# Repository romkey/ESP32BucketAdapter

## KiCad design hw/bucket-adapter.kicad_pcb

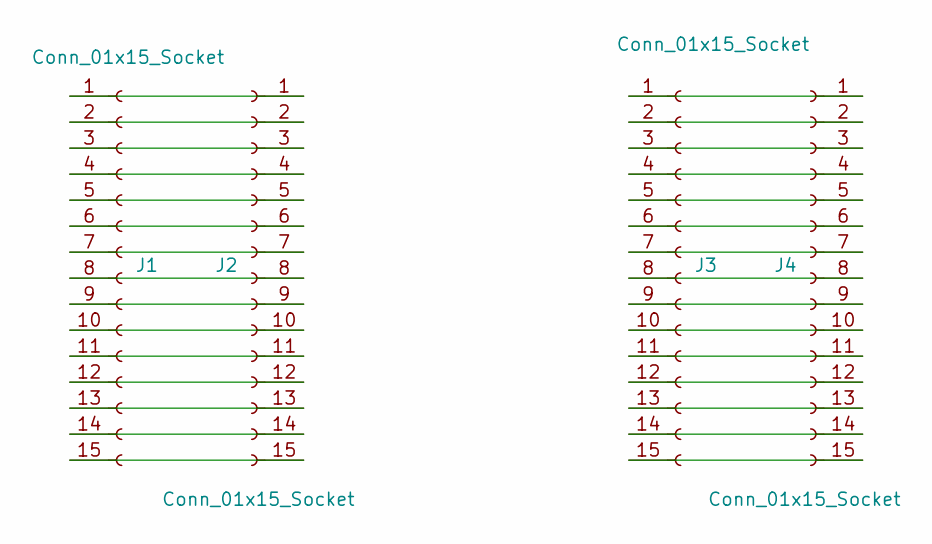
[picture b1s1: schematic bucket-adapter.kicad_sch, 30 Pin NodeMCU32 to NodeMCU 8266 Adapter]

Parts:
J1, J2, J3, J4: Conn_01x15_Socket; PinSocket_1x15_P2.54mm_Vertical

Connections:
unnamed: J1.1, J2.1
unnamed: J1.2, J2.2
unnamed: J1.3, J2.3
unnamed: J1.4, J2.4
unnamed: J1.5, J2.5
unnamed: J1.6, J2.6
unnamed: J1.7, J2.7
unnamed: J1.8, J2.8
unnamed: J1.9, J2.9
unnamed: J1.10, J2.10
unnamed: J1.11, J2.11
unnamed: J1.12, J2.12
unnamed: J1.13, J2.13
unnamed: J1.14, J2.14
unnamed: J1.15, J2.15
unnamed: J3.1, J4.1
unnamed: J3.2, J4.2
unnamed: J3.3, J4.3
unnamed: J3.4, J4.4
unnamed: J3.5, J4.5
unnamed: J3.6, J4.6
unnamed: J3.7, J4.7
unnamed: J3.8, J4.8
unnamed: J3.9, J4.9
unnamed: J3.10, J4.10
unnamed: J3.11, J4.11
unnamed: J3.12, J4.12
unnamed: J3.13, J4.13
unnamed: J3.14, J4.14
unnamed: J3.15, J4.15

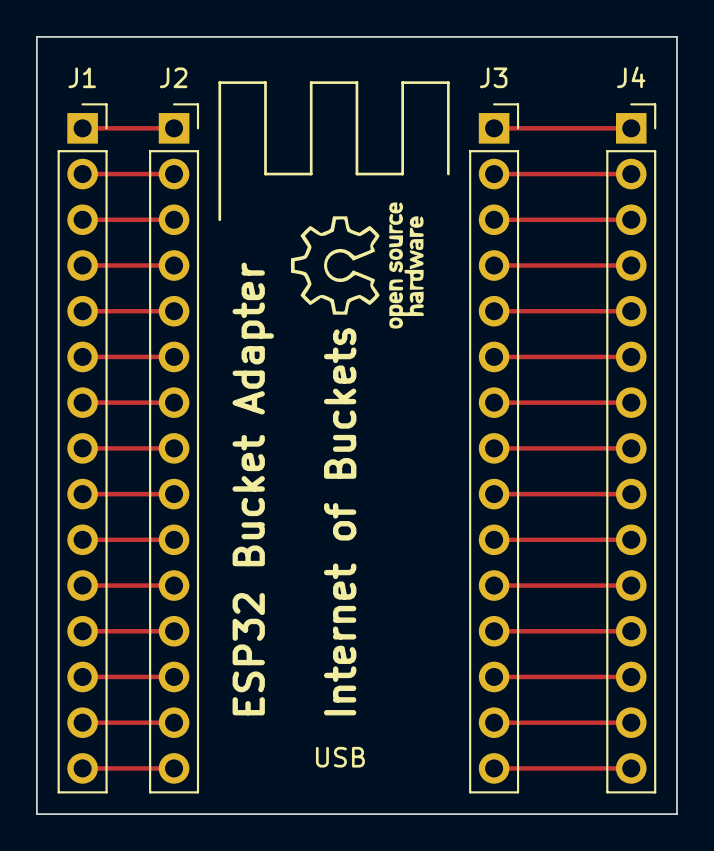
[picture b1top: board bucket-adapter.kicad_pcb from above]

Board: 2 copper layers, 35.6 x 43.2 mm, 4 parts (0 on the bottom side), 30 nets.

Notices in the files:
hw/bucket-adapter.kicad_sch:
Public domain, no license or liability implied
